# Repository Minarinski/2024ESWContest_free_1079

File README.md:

# 2024ESWContest_free_1079

## IoT-VehiCALL은 승객의 버스 탑승을 돕는 "승차벨" 시스템입니다.
### 대중교통 이용을 편리하게 하며, 교통약자의 접근성을 향상하고 버스 노선 운영을 효율적으로 할 수 있도록 합니다.

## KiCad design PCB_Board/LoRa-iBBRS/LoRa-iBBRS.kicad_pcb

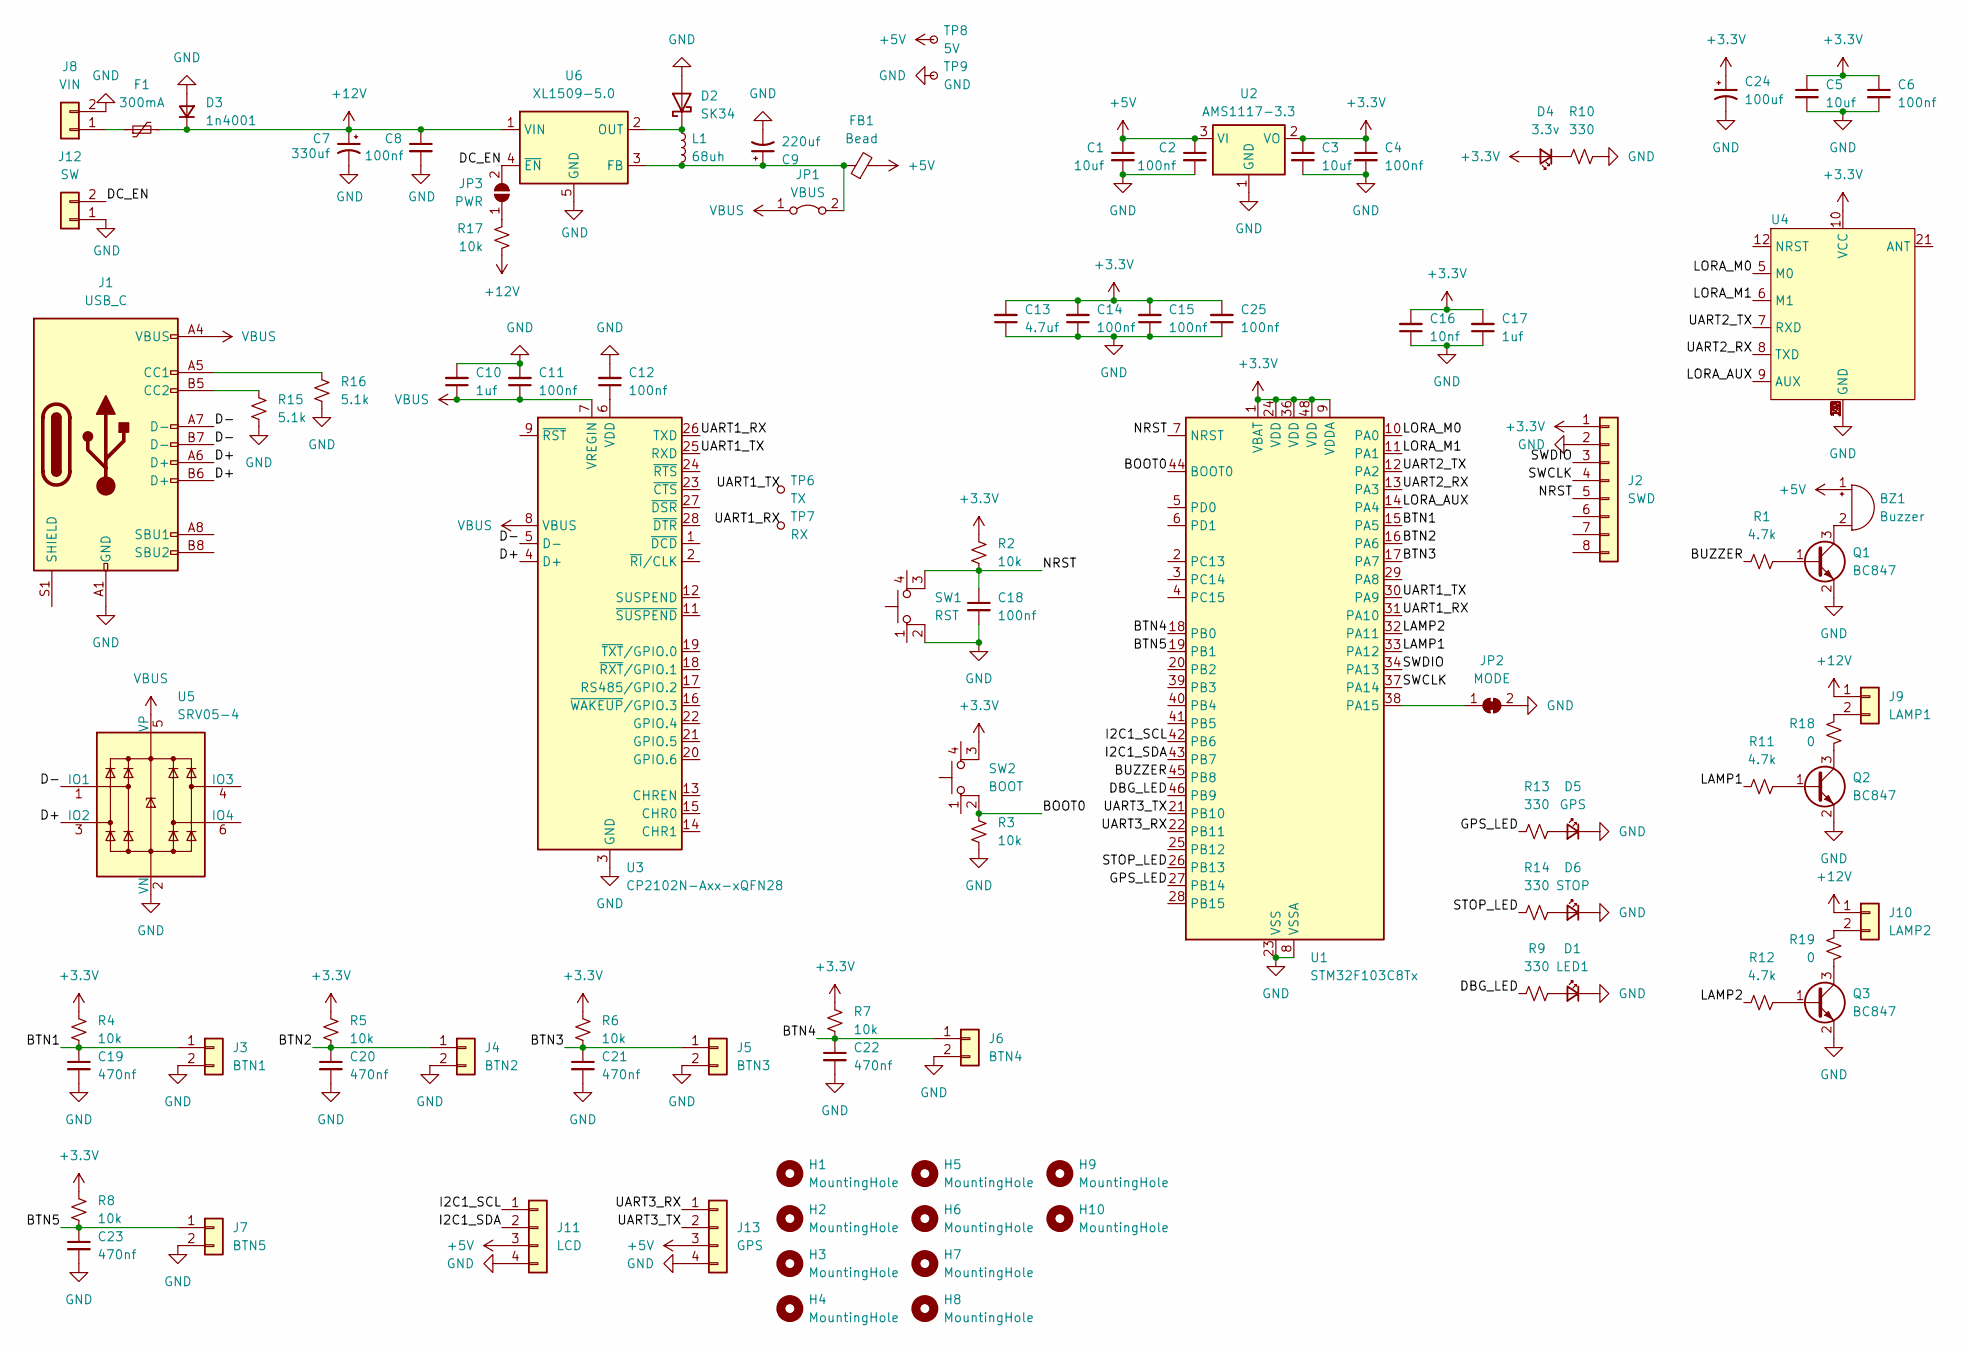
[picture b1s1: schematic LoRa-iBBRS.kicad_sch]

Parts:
BZ1: Buzzer; FQ-014
C1, C3, C5: 10uf; C_0603_1608Metric
C2, C4, C6, C8, C11, C12, C14, C15, C18, C25: 100nf; C_0603_1608Metric
C7: 330uf; CP_Elec_10x10.5; LCSC C336775
C9: 220uf; CP_Elec_8x10.5; LCSC C336709
C10, C17: 1uf; C_0603_1608Metric
C13: 4.7uf; C_0603_1608Metric
C16: 10nf; C_0603_1608Metric
C19, C20, C21, C22, C23: 470nf; C_0603_1608Metric
C24: 100uf; CP_Elec_8x6.5; LCSC C401616
D1: LED1; LED_0603_1608Metric
D2: SK34; D_SMA; LCSC C8678
D3: 1n4001; D_SMA
D4: 3.3v; LED_0603_1608Metric
D5: GPS; LED_D5.0mm
D6: STOP; LED_D5.0mm
F1: 300mA; Fuse_0603_1608Metric; LCSC C910820
FB1: Bead; Fuse_0603_1608Metric; LCSC C1002
H1, H2, H3, H4, H5, H6, H7, H8, H9, H10: MountingHole; MountingHole_3.2mm_M3
J1: USB_C; USB_C_Receptacle_GCT_USB4105-xx-A_16P_TopMnt_Horizontal; LCSC C2765186
J2: SWD; PinHeader_1x08_P2.54mm_Vertical
J3: BTN1; PhoenixContact_MC_1,5_2-G-3.81_1x02_P3.81mm_Horizontal; LCSC C507005
J4: BTN2; PhoenixContact_MC_1,5_2-G-3.81_1x02_P3.81mm_Horizontal; LCSC C507005
J5: BTN3; PhoenixContact_MC_1,5_2-G-3.81_1x02_P3.81mm_Horizontal; LCSC C507005
J6: BTN4; PhoenixContact_MC_1,5_2-G-3.81_1x02_P3.81mm_Horizontal; LCSC C507005
J7: BTN5; PhoenixContact_MC_1,5_2-G-3.81_1x02_P3.81mm_Horizontal; LCSC C507005
J8: VIN; BarrelJack_Horizontal
J9: LAMP1; QN22-LED
J10: LAMP2; QN22-LED
J11: LCD; Molex_PicoBlade_53398-0471_1x04-1MP_P1.25mm_Vertical; LCSC C234195
J12: SW; Molex_SPOX_5267-02A_1x02_P2.50mm_Vertical
J13: GPS; Molex_PicoBlade_53398-0471_1x04-1MP_P1.25mm_Vertical; LCSC C234195
JP1: VBUS; SolderJumper-2_P1.3mm_Bridged_RoundedPad1.0x1.5mm
JP2: MODE; SolderJumper-2_P1.3mm_Bridged_RoundedPad1.0x1.5mm
JP3: PWR; SolderJumper-2_P1.3mm_Open_RoundedPad1.0x1.5mm
L1: 68uh; Inductor_4.5x4mm; LCSC C324241
Q1, Q2, Q3: BC847; SOT-23; LCSC C181140
R1, R11, R12: 4.7k; R_0603_1608Metric
R2, R3, R4, R5, R6, R7, R8, R17: 10k; R_0603_1608Metric
R9, R10, R13, R14: 330; R_0603_1608Metric
R15, R16: 5.1k; R_0603_1608Metric
R18, R19: 0; R_0603_1608Metric
SW1: RST; SW_TS-1187A-B-A-B; LCSC C318884
SW2: BOOT; SW_TS-1187A-B-A-B; LCSC C318884
TP6: TX; TestPoint_THTPad_2.0x2.0mm_Drill1.0mm
TP7: RX; TestPoint_THTPad_2.0x2.0mm_Drill1.0mm
TP8: 5V; TestPoint_THTPad_2.0x2.0mm_Drill1.0mm
TP9: GND; TestPoint_THTPad_2.0x2.0mm_Drill1.0mm
U1: STM32F103C8Tx; LQFP-48_7x7mm_P0.5mm; LCSC C8734
U2: AMS1117-3.3; SOT-223-3_TabPin2; LCSC C6186
U3: CP2102N-Axx-xQFN28; QFN-28-1EP_5x5mm_P0.5mm_EP3.35x3.35mm; LCSC C6568
U4: E22-900T22S; LCSC C411289
U5: SRV05-4; SOT-23-6; LCSC C7420376
U6: XL1509-5.0; SOIC-8_3.9x4.9mm_P1.27mm; LCSC C61063

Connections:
+3.3V: C3.1, C4.1, C5.1, C6.1, C13.2, C14.2, C15.2, C16.2, C17.2, C24.1, C25.2, D4.2 (A), J2.1, R2.1, R4.1, R5.1, R6.1, R7.1, R8.1, SW2.3 (K), U1.1 (VBAT), U1.9 (VDDA), U1.24 (VDD), U1.36 (VDD), U1.48 (VDD), U2.2 (VO), U4.10 (VCC)
+5V: BZ1.1 (+), C1.1, C2.1, FB1.2, J11.3, J13.3, TP8.1, U2.3 (VI)
+12V: C7.1, C8.1, D3.1 (K), F1.2, J9.1, J10.1, R17.2, U6.1 (VIN)
/BOOT0: R3.1, SW2.2, U1.44 (BOOT0)
/BTN1: C19.1, J3.1, R4.2, U1.15 (PA5)
/BTN2: C20.1, J4.1, R5.2, U1.16 (PA6)
/BTN3: C21.1, J5.1, R6.2, U1.17 (PA7)
/BTN4: C22.1, J6.1, R7.2, U1.18 (PB0)
/BTN5: C23.1, J7.1, R8.2, U1.19 (PB1)
/BUZZER: R1.1, U1.45 (PB8)
/D+: J1.A6 (D+), J1.B6 (D+), U3.4 (D+), U5.3 (IO2)
/D-: J1.A7 (D-), J1.B7 (D-), U3.5 (D-), U5.1 (IO1)
/DBG_LED: R9.1, U1.46 (PB9)
/DC_EN: J12.2, JP3.2 (B), U6.4 (~EN)
/GPS_LED: R13.1, U1.27 (PB14)
/I2C1_SCL: J11.1, U1.42 (PB6)
/I2C1_SDA: J11.2, U1.43 (PB7)
/LAMP1: R11.1, U1.33 (PA12)
/LAMP2: R12.1, U1.32 (PA11)
/LORA_AUX: U1.14 (PA4), U4.9 (AUX)
/LORA_M0: U1.10 (PA0), U4.5 (M0)
/LORA_M1: U1.11 (PA1), U4.6 (M1)
/NRST: C18.1, J2.5, R2.2, SW1.3 (K), U1.7 (NRST)
/STOP_LED: R14.1, U1.26 (PB13)
/SWCLK: J2.4, U1.37 (PA14)
/SWDIO: J2.3, U1.34 (PA13)
/UART1_RX: TP7.1, U1.31 (PA10), U3.26 (TXD)
/UART1_TX: TP6.1, U1.30 (PA9), U3.25 (RXD)
/UART2_RX: U1.13 (PA3), U4.8 (TXD)
/UART2_TX: U1.12 (PA2), U4.7 (RXD)
/UART3_RX: J13.1, U1.22 (PB11)
/UART3_TX: J13.2, U1.21 (PB10)
GND: C1.2, C2.2, C3.2, C4.2, C5.2, C6.2, C7.2, C8.2, C9.2, C10.2, C11.2, C12.2, C13.1, C14.1, C15.1, C16.1, C17.1, C18.2, C19.2, C20.2, C21.2, C22.2, C23.2, C24.2, C25.1, D1.1 (K), D2.2 (A), D3.2 (A), D5.1 (K), D6.1 (K), J1.A1 (GND), J1.A12 (GND), J1.B1 (GND), J1.B12 (GND), J2.2, J3.2, J4.2, J5.2, J6.2, J7.2, J8.2, J11.4, J12.1, J13.4, JP2.2 (B), Q1.2 (E), Q2.2 (E), Q3.2 (E), R3.2, R10.2, R15.2, R16.2, SW1.2, TP9.1, U1.8 (VSSA), U1.23 (VSS), U1.35 (VSS), U1.47 (VSS), U2.1 (GND), U3.3 (GND), U3.29 (GND), U4.1 (GND), U4.2 (GND), U4.3 (GND), U4.4 (GND), U4.11 (GND), U4.13 (GND), U4.19 (GND), U4.20 (GND), U4.22 (GND), U5.2 (VN), U6.5 (GND), U6.6 (GND), U6.7 (GND), U6.8 (GND)
unnamed: BZ1.2 (-), Q1.3 (C)
unnamed: D1.2 (A), R9.2
unnamed: D2.1 (K), L1.1, U6.2 (OUT)
unnamed: D4.1 (K), R10.1
unnamed: D5.2 (A), R13.2
unnamed: D6.2 (A), R14.2
unnamed: J1.A5 (CC1), R16.1
unnamed: J1.B5 (CC2), R15.1
unnamed: F1.1, J8.1
unnamed: J9.2, R18.2
unnamed: J10.2, R19.2
unnamed: C9.1, FB1.1, JP1.2 (B), L1.2, U6.3 (FB)
unnamed: JP2.1 (A), U1.38 (PA15)
unnamed: JP3.1 (A), R17.1
unnamed: Q1.1 (B), R1.2
unnamed: Q2.1 (B), R11.2
unnamed: Q2.3 (C), R18.1
unnamed: Q3.1 (B), R12.2
unnamed: Q3.3 (C), R19.1
unnamed: C12.1, U3.6 (VDD)
VBUS: C10.1, C11.1, J1.A4 (VBUS), J1.A9 (VBUS), J1.B4 (VBUS), J1.B9 (VBUS), JP1.1 (A), U3.7 (VREGIN), U3.8 (VBUS), U5.5 (VP)

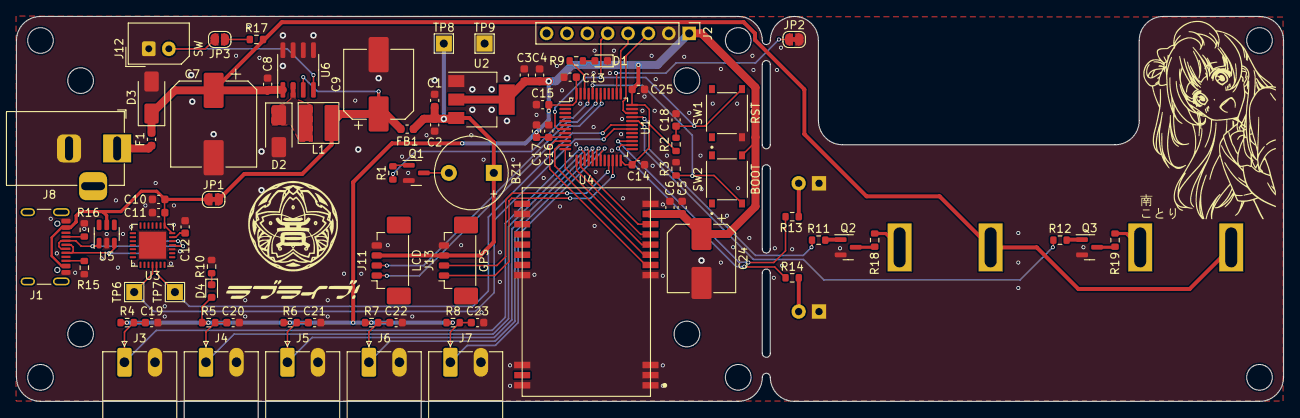
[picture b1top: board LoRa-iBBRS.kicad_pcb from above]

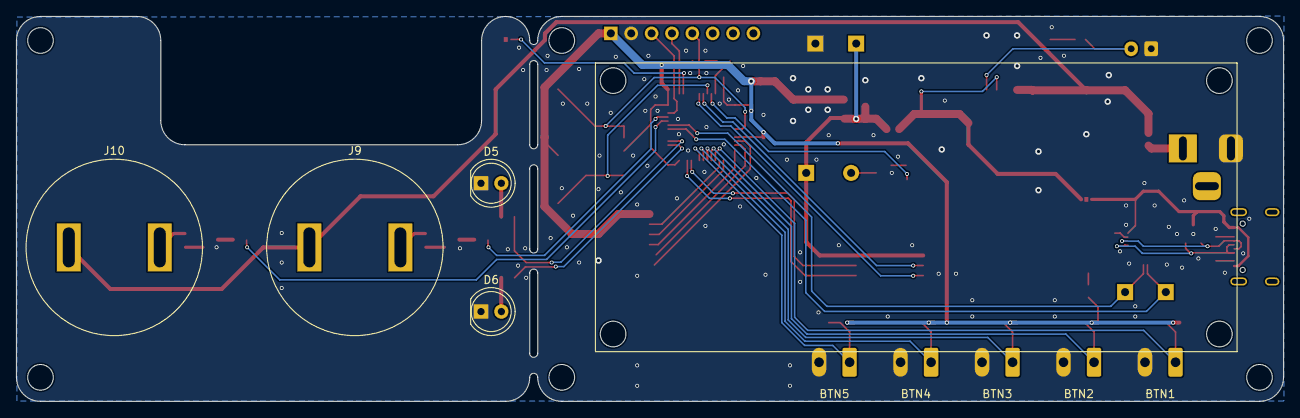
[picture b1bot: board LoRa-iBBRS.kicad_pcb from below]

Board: 2 copper layers, 158.0 x 48.0 mm, 95 parts (8 on the bottom side), 54 nets.

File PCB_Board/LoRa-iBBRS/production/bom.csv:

Designator,Footprint,Quantity,Value,LCSC Part #
"C1, C3, C5",0603,3,10uf,
"C10, C17",0603,2,1uf,
"C11, C12, C14, C15, C18, C2, C25, C4, C6, C8",0603,10,100nf,
C13,0603,1,4.7uf,
C16,0603,1,10nf,
"C19, C20, C21, C22, C23",0603,5,470nf,
C24,CP_Elec_8x6.5,1,100uf,C401616
C7,CP_Elec_10x10.5,1,330uf,C336775
C9,CP_Elec_8x10.5,1,220uf,C336709
D1,0603,1,LED1,
D2,D_SMA,1,SK34,C8678
D3,D_SMA,1,1n4001,
D4,0603,1,3.3v,
F1,0603,1,300mA,C910820
FB1,0603,1,Bead,C1002
J1,USB_C_Receptacle_GCT_USB4105-xx-A_16P_TopMnt_Horizontal,1,USB_C,C2765186
J11,Molex_PicoBlade_53398-0471_1x04-1MP_P1.25mm_Vertical,1,LCD,C234195
J13,Molex_PicoBlade_53398-0471_1x04-1MP_P1.25mm_Vertical,1,GPS,C234195
J3,"PhoenixContact_MC_1,5_2-G-3.81_1x02_P3.81mm_Horizontal",1,BTN1,C507005
J4,"PhoenixContact_MC_1,5_2-G-3.81_1x02_P3.81mm_Horizontal",1,BTN2,C507005
J5,"PhoenixContact_MC_1,5_2-G-3.81_1x02_P3.81mm_Horizontal",1,BTN3,C507005
J6,"PhoenixContact_MC_1,5_2-G-3.81_1x02_P3.81mm_Horizontal",1,BTN4,C507005
J7,"PhoenixContact_MC_1,5_2-G-3.81_1x02_P3.81mm_Horizontal",1,BTN5,C507005
J8,BarrelJack_Horizontal,1,VIN,
L1,Inductor_4.5x4mm,1,68uh,C324241
"Q1, Q2, Q3",SOT-23,3,BC847,C181140
"R1, R11, R12",0603,3,4.7k,
"R10, R13, R14, R9",0603,4,330,
"R15, R16",0603,2,5.1k,
"R17, R2, R3, R4, R5, R6, R7, R8",0603,8,10k,
"R18, R19",0603,2,0,
SW1,SW_TS-1187A-B-A-B,1,RST,C318884
SW2,SW_TS-1187A-B-A-B,1,BOOT,C318884
U1,LQFP-48_7x7mm_P0.5mm,1,STM32F103C8Tx,C8734
U2,SOT-223-3_TabPin2,1,AMS1117-3.3,C6186
U3,QFN-28-1EP_5x5mm_P0.5mm_EP3.35x3.35mm,1,CP2102N-Axx-xQFN28,C6568
U4,E22-900T22S,1,~,C411289
U5,SOT-23-6,1,SRV05-4,C7420376
U6,SOIC-8_3.9x4.9mm_P1.27mm,1,XL1509-5.0,C61063

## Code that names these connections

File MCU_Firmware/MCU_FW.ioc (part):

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Mcu.Name=STM32F103C(8-B)Tx
Mcu.Package=LQFP48
Mcu.UserName=STM32F103C8Tx
PA0-WKUP.GPIOParameters=GPIO_Label
PA0-WKUP.GPIO_Label=LORA_M0
PA0-WKUP.Signal=GPIO_Output
PA1.GPIOParameters=GPIO_Label
PA1.GPIO_Label=LORA_M1
PA1.Signal=GPIO_Output
PA10.Mode=Asynchronous
PA10.Signal=USART1_RX
PA11.GPIOParameters=GPIO_Label
PA11.GPIO_Label=LAMP2
PA11.Signal=GPIO_Output
PA12.GPIOParameters=GPIO_Label
PA12.GPIO_Label=LAMP1
PA12.Signal=GPIO_Output
PA13.Mode=Serial_Wire
PA13.Signal=SYS_JTMS-SWDIO
PA14.Mode=Serial_Wire
PA14.Signal=SYS_JTCK-SWCLK
PA15.GPIOParameters=GPIO_PuPd,GPIO_Label
PA15.GPIO_Label=MODE_SLCT
PA15.GPIO_PuPd=GPIO_PULLUP
PA15.Signal=GPIO_Input
PA2.Mode=Asynchronous
PA2.Signal=USART2_TX
PA3.Mode=Asynchronous
PA3.Signal=USART2_RX
PA4.GPIOParameters=GPIO_Label
PA4.GPIO_Label=LORA_AUX
PA4.Signal=GPIO_Input
PA5.GPIOParameters=GPIO_Label,GPIO_ModeDefaultEXTI
PA5.GPIO_Label=BTN1
PA5.GPIO_ModeDefaultEXTI=GPIO_MODE_IT_RISING_FALLING
PA5.Signal=GPXTI5
PA6.GPIOParameters=GPIO_Label,GPIO_ModeDefaultEXTI
PA6.GPIO_Label=BTN2
PA6.GPIO_ModeDefaultEXTI=GPIO_MODE_IT_RISING_FALLING
PA6.Signal=GPXTI6
PA7.GPIOParameters=GPIO_Label,GPIO_ModeDefaultEXTI
PA7.GPIO_Label=BTN3
PA7.GPIO_ModeDefaultEXTI=GPIO_MODE_IT_RISING_FALLING
PA7.Signal=GPXTI7
PA9.Mode=Asynchronous
PA9.Signal=USART1_TX
PB0.GPIOParameters=GPIO_Label,GPIO_ModeDefaultEXTI
PB0.GPIO_Label=BTN4
PB0.GPIO_ModeDefaultEXTI=GPIO_MODE_IT_RISING_FALLING
PB0.Signal=GPXTI0
PB1.GPIOParameters=GPIO_Label,GPIO_ModeDefaultEXTI
PB1.GPIO_Label=BTN5
PB1.GPIO_ModeDefaultEXTI=GPIO_MODE_IT_RISING_FALLING
PB1.Signal=GPXTI1
PB10.Mode=Asynchronous
PB10.Signal=USART3_TX
PB11.Mode=Asynchronous
PB11.Signal=USART3_RX
PB13.GPIOParameters=GPIO_Label
PB13.GPIO_Label=STOP_LED
PB13.Signal=GPIO_Output
PB14.GPIOParameters=GPIO_Label
PB14.GPIO_Label=GPS_LED
PB14.Signal=GPIO_Output
PB6.Mode=I2C
PB6.Signal=I2C1_SCL
PB7.Mode=I2C
PB7.Signal=I2C1_SDA
PB8.GPIOParameters=GPIO_Label
PB8.GPIO_Label=BUZZER
PB8.Signal=GPIO_Output
PB9.GPIOParameters=GPIO_Label
PB9.GPIO_Label=DBG_LED
PB9.Signal=GPIO_Output
RCC.SYSCLKFreq_VALUE=16000000
RCC.SYSCLKSource=RCC_SYSCLKSOURCE_PLLCLK
board=custom

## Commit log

2024-08-30 폴더 구성
2024-08-30 BusDataLoader
2024-08-30 BusInfo
2024-08-30 MCU_Firmware
2024-09-05 PCB 파일 업로드, 이미지 추가
2024-09-05 Readme 수정
2024-09-05 Release EXE 파일 추가
2024-09-06 주석 unicode error해결
2024-10-11 예외처리 및 정류장 변경
2024-10-21 시연용 코드 개선
2024-10-21 시연용 F/W 개선
2024-10-21 txt 형식 변경
2024-10-21 각종 오류 해결
2024-10-21 카운트다운 기능 추가
2024-10-21 카운트다운 기능 오류해결
2024-10-21 페이지 고정 기능 추가
2024-10-21 mutex?
2024-10-21 mutex??
2024-10-22 Qmutex
2024-10-22 api에도 mutex적용
2024-10-22 운행대기 음성 제외
2024-10-22 충돌 해결
2024-10-22 isSpeaked 유지
2024-10-22 중복음성출력 해결
2024-10-22 예외처리(마을 및 2002)
2024-10-22 2002 개선
2024-10-22 대사 변경
2024-10-22 예외처리
2024-10-22 다음 정류장 기능
2024-10-22 멈추는 오류 해결
2024-10-22 only ars
2024-10-22 f5 pageFix
2024-10-22 기기 예외처리 추가 및 BusDataLoader 예외처리
2024-10-22 초기 페이지 설정
